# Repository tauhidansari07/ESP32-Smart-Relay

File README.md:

# ESP32-Smart-Relay: Open-Source Smart Relay Module
> A compact, production-ready 220V AC smart plug relay module built around the ESP32-C3, featuring full galvanic isolation, integrated AC-DC conversion, and exposed UART programming pins.
> 
## ⚡ Overview
This project is an open-source hardware design for a 10A Wi-Fi/Bluetooth smart relay. It is designed to sit between mains power and everyday appliances (lamps, fans, heaters), allowing for local or cloud-based smart home control.
Unlike many commercial closed-source smart plugs, this board exposes a standard 6-pin UART header, making it trivially easy to flash with custom firmware like **ESPHome**, **Tasmota**, or your own custom Arduino/C++ code.
## 🛠️ Hardware Features
 * **Microcontroller:** ESP32-C3-WROOM-02-H4 (RISC-V, Wi-Fi 4, Bluetooth 5 LE).
 * **Power Supply:** Onboard Hi-Link HLK-PM01 5V step-down module with an AMS1117 3.3V LDO for clean logic power.
 * **Galvanic Isolation:** The low-voltage ESP32 logic is physically and electrically isolated from the high-voltage relay coil using a **PC817 Optocoupler**.
 * **Switching Capacity:** 10A @ 250V AC Mechanical Relay (Songle SRD-05VDC), capable of switching up to 2200W.
 * **Safety First:** Includes a 10A slow-blow inline fuse, a Metal Oxide Varistor (MOV) for surge protection, and strict PCB creepage/clearance routing.
 * **Developer Friendly:** Dedicated 6-pin 2.54mm pitch programming header (3V3, GND, TX, RX, IO9/BOOT, EN/RESET).
## ⚠️ DANGER: HIGH VOLTAGE WARNING
**This project involves working with 220V-240V AC Mains Electricity.**
Mains voltage is lethal and can cause serious injury, death, or fire if mishandled. This repository is provided for educational and prototyping purposes only.
 * Never touch the PCB while it is connected to wall power.
 * Ensure your PCB manufacturer properly mills the isolation slots between the high-voltage and low-voltage sections.
 * Always house the final board in a non-conductive, fire-retardant enclosure.
## 🗜️ Flashing the ESP32-C3
To flash custom firmware (like ESPHome):
 1. Connect a 3.3V FTDI / USB-to-Serial programmer to the UART header.
   * *Note: Programmer TX goes to Board RX (Pin 11). Programmer RX goes to Board TX (Pin 12).*
 2. Do **NOT** connect AC mains power while the FTDI is plugged in. Power the board via the 3.3V pin on the header.
 3. To enter flash mode, hold IO9 to GND, briefly pulse EN to GND, then release IO9.
## 📁 Repository Contents
 * /Hardware - KiCad / EDA schematic and PCB layout files.
 * /Firmware - Example Arduino sketches and ESPHome .yaml configuration files.
 * /Enclosure - (Optional) 3D printable STL files for the housing.

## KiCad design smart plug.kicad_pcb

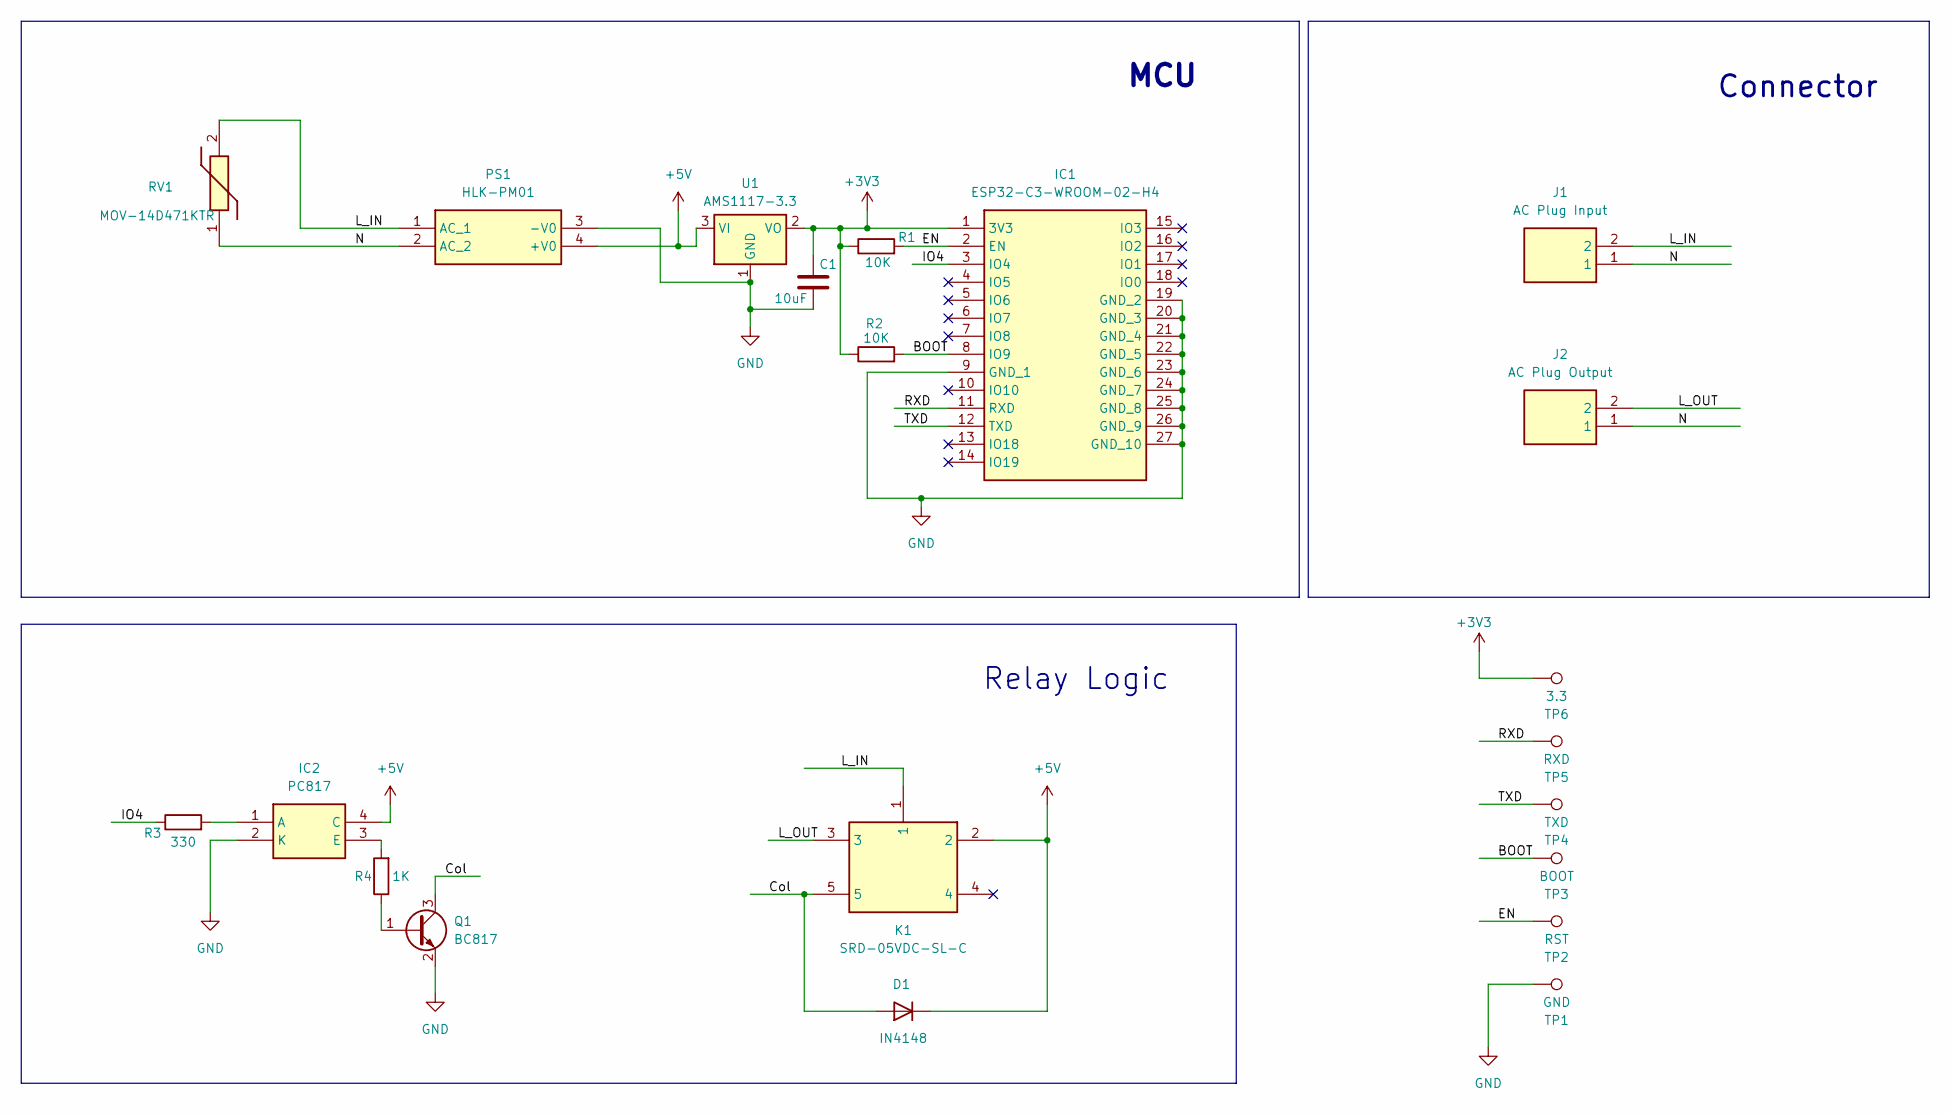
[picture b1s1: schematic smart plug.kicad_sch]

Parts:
C1: 10uF; C_0805_2012Metric_Pad1.18x1.45mm_HandSolder
D1: IN4148; D_SOD-128
IC1: ESP32-C3-WROOM-02-H4; ESP32C3WROOM02H4; Manufacturer_Part_Number ESP32-C3-WROOM-02-H4; Mouser Part Number 356-ESP32C3WROOM02H4
IC2: PC817; DIP810W60P254L460H500Q4N; Manufacturer_Part_Number PC817
J1: AC Plug Input; 2828372; Manufacturer_Part_Number 282837-2; Mouser Part Number 571-2828372
J2: AC Plug Output; 2828372; Manufacturer_Part_Number 282837-2; Mouser Part Number 571-2828372
K1: SRD-05VDC-SL-C; SRD; Manufacturer_Part_Number SRD-05VDC-SL-C
PS1: HLK-PM01; HLKPM01; Manufacturer_Part_Number HLK-PM01
Q1: BC817; SOT-23
R1, R2: 10K; R_0402_1005Metric_Pad0.72x0.64mm_HandSolder
R3: 330; R_0402_1005Metric_Pad0.72x0.64mm_HandSolder
R4: 1K; R_0402_1005Metric_Pad0.72x0.64mm_HandSolder
RV1: MOV-14D471KTR; MOV14D471K; Manufacturer_Part_Number MOV-14D471KTR; Mouser Part Number 652-MOV-14D471KTR
TP1: GND; Pin_D1.0mm_L10.0mm
TP2: RST; Pin_D1.0mm_L10.0mm
TP3: BOOT; Pin_D1.0mm_L10.0mm
TP4: TXD; Pin_D1.0mm_L10.0mm
TP5: RXD; Pin_D1.0mm_L10.0mm
TP6: 3.3; Pin_D1.0mm_L10.0mm
U1: AMS1117-3.3; SOT-223-3_TabPin2

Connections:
+3V3: C1.1, IC1.1 (3V3), R1.1, R2.1, TP6.1, U1.2 (VO)
+5V: D1.1 (K), IC2.4 (C), K1.2, PS1.4 (+V0), U1.3 (VI)
/BOOT: IC1.8 (IO9), R2.2, TP3.1
/Col: D1.2 (A), K1.5, Q1.3 (C)
/EN: IC1.2 (EN), R1.2, TP2.1
/IO4: IC1.3 (IO4), R3.1
/L_IN: J1.2, K1.1, PS1.1 (AC_1), RV1.2
/L_OUT: J2.2, K1.3
/N: J1.1, J2.1, PS1.2 (AC_2), RV1.1
/RXD: IC1.11 (RXD), TP5.1
/TXD: IC1.12 (TXD), TP4.1
GND: C1.2, IC1.9 (GND_1), IC1.19 (GND_2), IC1.20 (GND_3), IC1.21 (GND_4), IC1.22 (GND_5), IC1.23 (GND_6), IC1.24 (GND_7), IC1.25 (GND_8), IC1.26 (GND_9), IC1.27 (GND_10), IC2.2 (K), PS1.3 (-V0), Q1.2 (E), TP1.1, U1.1 (GND)
unnamed: IC2.1 (A), R3.2
unnamed: IC2.3 (E), R4.2
unnamed: Q1.1 (B), R4.1

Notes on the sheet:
Relay Logic
Connector
MCU

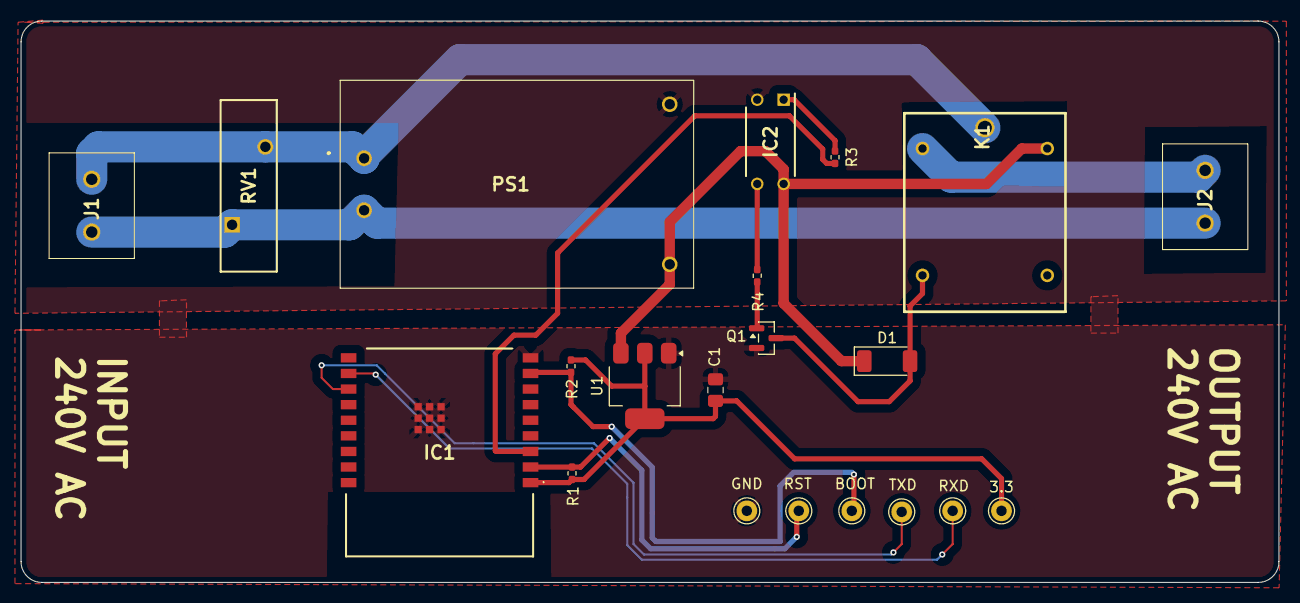
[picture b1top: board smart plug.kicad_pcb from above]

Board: 2 copper layers, 121.0 x 54.0 mm, 21 parts (0 on the bottom side), 15 nets.
